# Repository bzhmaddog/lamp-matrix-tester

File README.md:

# Pinball lamp matrix tester

A Pinball lamp matrix testing board using a 1088AS 8x8 led matrix module

Bom:

- 8x resistors (from 300Ohms to whatever you want depending on the voltage you apply and brightness you want).
- 1x 1088AS module with 8x8 leds (32mm x 32mm).
- 2x 1x8 female pin header.
- 2x 1x8pins horizontal header (2.54mm).

Notes:
- Resistors values ranges from 300Ohms to whatever value you want  depending on the voltage you apply and brightness you want to achieve.
- The female pin headers act as a socket for the 1088AS for easy replacement and also elevate it above the resistors.

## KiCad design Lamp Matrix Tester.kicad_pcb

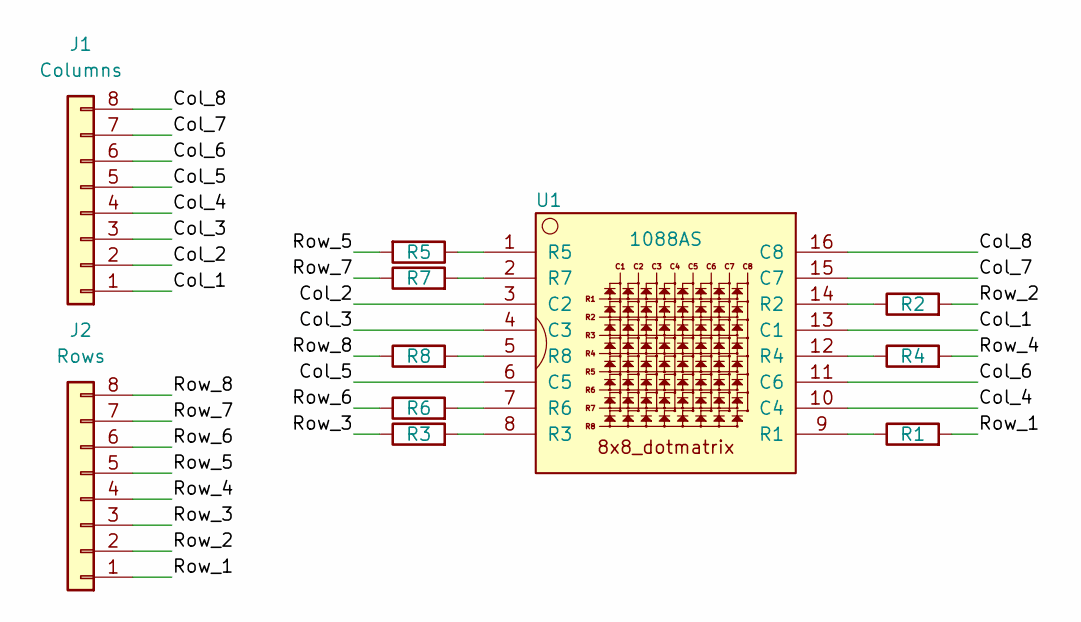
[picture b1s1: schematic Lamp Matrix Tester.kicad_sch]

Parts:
J1: Columns; PinHeader_1x08_P2.54mm_Horizontal
J2: Rows; PinHeader_1x08_P2.54mm_Horizontal
R1, R2, R3, R4, R5, R6, R7, R8: R; R_Axial_DIN0204_L3.6mm_D1.6mm_P7.62mm_Horizontal
U1: 1088AS; Led_1088AS_8x8_P2.54mm

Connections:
/Col_1: J1.1, U1.13 (C1)
/Col_2: J1.2, U1.3 (C2)
/Col_3: J1.3, U1.4 (C3)
/Col_4: J1.4, U1.10 (C4)
/Col_5: J1.5, U1.6 (C5)
/Col_6: J1.6, U1.11 (C6)
/Col_7: J1.7, U1.15 (C7)
/Col_8: J1.8, U1.16 (C8)
/Row_1: J2.1, R1.2
/Row_2: J2.2, R2.2
/Row_3: J2.3, R3.1
/Row_4: J2.4, R4.2
/Row_5: J2.5, R5.2
/Row_6: J2.6, R6.1
/Row_7: J2.7, R7.1
/Row_8: J2.8, R8.1
unnamed: R1.1, U1.9 (R1)
unnamed: R2.1, U1.14 (R2)
unnamed: R3.2, U1.8 (R3)
unnamed: R4.1, U1.12 (R4)
unnamed: R5.1, U1.1 (R5)
unnamed: R6.2, U1.7 (R6)
unnamed: R7.2, U1.2 (R7)
unnamed: R8.2, U1.5 (R8)

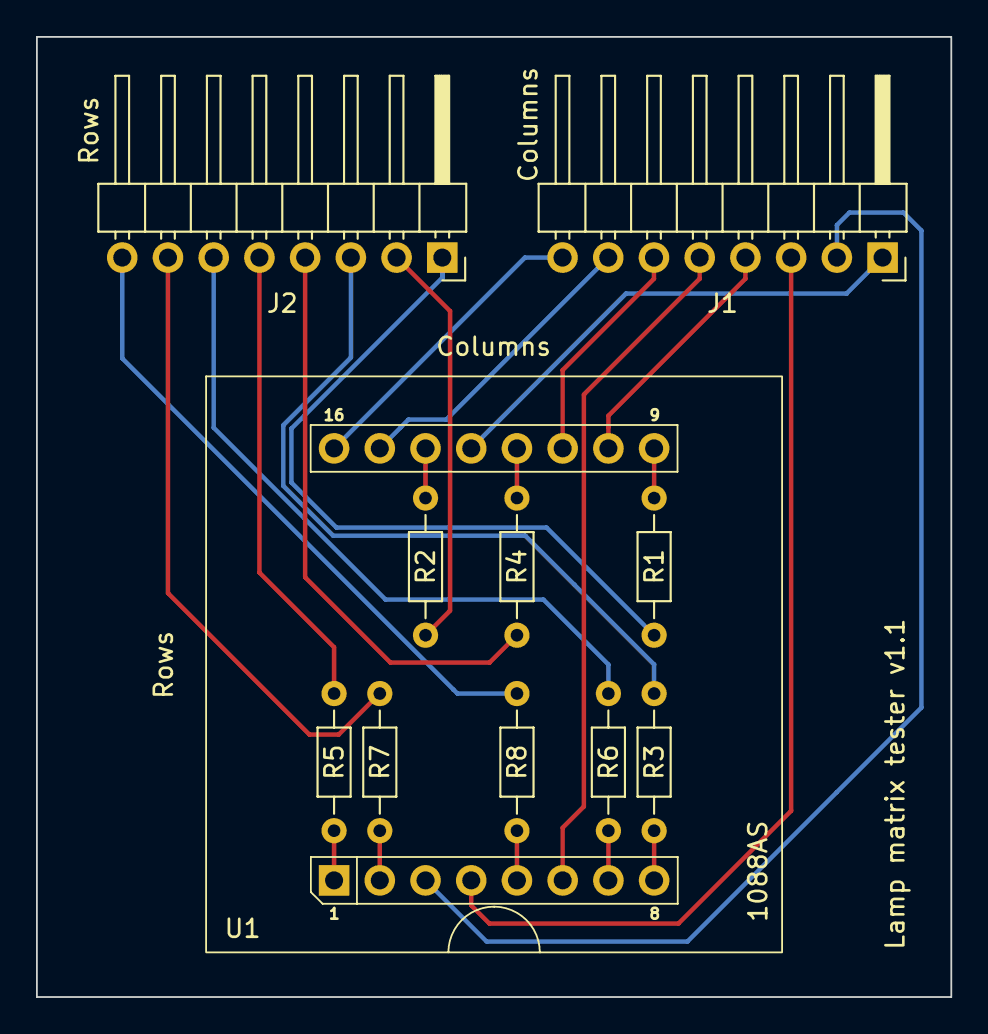
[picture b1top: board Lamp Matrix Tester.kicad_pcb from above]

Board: 2 copper layers, 50.8 x 53.3 mm, 11 parts (0 on the bottom side), 24 nets.

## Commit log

2024-03-09 Initial commit v1.0
2024-03-09 Fixed README.md
2024-03-09 Removed LICENSE
2024-03-09 re-create LICENCE
2024-03-11 Migrate to Kicad 8 + Included symbol/footprint and 3D model for 1088AS module
2024-03-13 Migrated to kicad8 + Added textured 3D model of the 1088AS module
2024-03-13 Removed gerber files from repo
2024-03-16 V1.1 - Swapped rows and cols position and pinout
